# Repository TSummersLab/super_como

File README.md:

# Super COMO
Super COMO is an autonomous car platfrom at the University of Texas at Dallas. It is a hardware upgrade over the [COMO platform](https://github.com/TSummersLab/como).

Check out [our website](https://omarkabbas.github.io/supercomo/) for details about car assembly, build, and other guides and tutorials.

## Installation Guide

Before installing the Super COMO packages, perform a full JetPack installation on the Jetson TX2. For the package, JetPack 3.2.1 was installed. 

After installing JetPack, follow the steps below to setup Super COMO.

1. Configure repositories:
Configure repositories to allow "restricted," "universe," and "multiverse." Do this by following the instructions in [this link](https://help.ubuntu.com/community/Repositories/Ubuntu).

2. Clone super_como :
Clone the repository to your home directory. In a terminal window run:
```
cd ~ && git clone https://github.com/The-SS/super_como
```

3. Navigate to setup folder:
In terminal, navigate to the `setup` folder in `super_como` by running:
``` 
cd ~/super_como/setup
```

4. Configure git (if not configured):
Configure git either manually or by running `git_config_setup.sh`. You can run the setup file as follows:
```
./git_config_setup.sh
```

5. Run the following scripts:
```
./install_programs.sh

./install_ros.sh

```

6. Download and install the ZED SDK:
- Go to the [ZED downloads](https://www.stereolabs.com/developers/release/#sdkdownloads_anchor) website and download the [ZED SDK for Jetson TX2 with JetPack 3.2 and CUDA 9](https://download.stereolabs.com/zedsdk/2.7/tegrax2).

- Once it downloads, either used `chmod +x <file_name>` to make the file and executable or right click it --> permissions --> allow executing file as a program.

- Run the script by `cd` to file location in a terminal and typing `./` followed by the file name.

7. Setup the device rules:
Run the rules set up script:
```
sudo ./rules_setup.sh
```

This script will reload the rules, but we recommend restarting the machine to ensure that the rules are in effect.

8. Run the build script:
The `build.sh` script at the root of the super_como package builds the catkin workspace. In a terminal window, navigate to the root of the super_como package then run the following command:
```
cd ~/super_como
./build.sh
```

9. Generate the `ros_lib` libraries for arduino:
- Go the the Arduino `libraries` direcotry: 
```
cd ~/arduino-1.8.7/libraries
``` 
- Remove any previous `ros_lib` directory:
```
rm -fr ros_lib
```
- Generate the new libraries:
```
rosrun rosserial_arduino make_libraries.py .
```

For more details see the Install ros_lib into the Arduino Environment section [here](http://wiki.ros.org/rosserial_arduino/Tutorials/Arduino%20IDE%20Setup).

10. Source the workspace:
Every time a new terminal window is open you have to source your workspace.
```
source ~/super_como/workspace/devel/setup.bash
```
Alternatively, you can add the above to your bashrc file to avoid having to run it every time. To do that, run the following in a terminal.
```
echo "source ~/super_como/workspace/devel/setup.bash" >> ~/.bashrc
```
Once this runs you have to restart your terminal or source the bashrc file as follows:
```
source ~/.bashrc
```

11. Add the Lidar to ethernet networks:
- Open `Network Connections`.
- Click on `Add`.
- In the new window do the following:
	- Change the connection name to `lidar`
	- In the `General` tab, check the `Automatically connect to this network when it is available` and `All users may connect to this network` options
	- In the `IPv4 Settings` tab, change the `method` to `Manual` and add the following in `Addresses`:
		- address: 192.168.0.15
		- netmask: 255.255.255.0 (this will change to 24)
		- leave the `gateway` field empty
	- Click save.

12. Edit the USB port names:
The rules file generated by `rules_setup.sh` creates symbolic links for devices that should be used instead of the port names generated by Linux. The full list of symbolic links found in `/etc/udev/rules/99-device-rules.rules` is:
- `/dev/imu`: IMU
- `/dev/vesc`: VESC 
- `/dev/teensy`: Teensy
- `/dev/gps`: GPS module
- `/dev/elp/back`: back elp camera
- `/dev/elp/right`: righ elp camera
- `/dev/elp/left`: left elp camera
- `/dev/elp/front`: front elp camera

These links should be used in the package (instead of `/dev/ttyUSB*`, `/dev/ttyACM*`, or `/dev/video*`). Make the following modifications to the package:
- In `~/super_como/super_como/workspace/src/racecar/racecar/config/racecar-v2/vesc.yaml` change the `port` parameter under `vesc_driver` to `/dev/vesc`.
- In `~/super_como/workspace/src/razor_imu_9dof/config/razor.yaml` change the `port` parameter to `/dev/imu`.
- In `~/super_como/workspace/src/razor_imu_9dof/nodes/imu_node.py` change the `default_port` variable to `'/dev/imu'` (line 110). The updated line should be: `default_port='/dev/imu'`.

13. If running YOLO, change the `darknet_ros` camera topic: 
In `~/super_como/workspace/src/darknet_ros/darknet_ros/config/ros.yaml` change the `topic` parameter under `camera_reading` in `subscribers` to the desired image topic. For example that could be the `/zed/left/image_raw_color` topic if using the ZED or ZED mini cameras. Check the [YOLO github repository](https://github.com/leggedrobotics/darknet_ros/tree/7bc7ec0517b7107712da998f975584c88ed15f77) for more details.

## Operating the Package
Operating the package is a two step process:
1. Starting the sensors and hardware
2. Starting an autonomous feature
This decoupling allows for easy switching between autonomous features wihtout having to restart all sensor operation

#### To Start the Sensors and Hardware
1. Open `super_como/workspace/src/hardware_interface/launch/super_como.launch` and edit the `On/Off Switches` section (and save the changes). 
	- Setting the default value to `true` will start the component
	- Setting the default value to `false` will skip starting the component
2. Run the following in a terminal window:
```
roslaunch hardware_interface super_como.launch
```

The super_como.launch provides an all-in-one solution to starting all hardware components. Nonetheless, individual scripts can be launched. Any of the scripts in `super_como/workspace/src/hardware_interface/launch` or any of the other packages in workspace can be run individually to control a single (or multiple) device(s).

#### To Start an Autonomous Feature
1. Determine what application to run and edit the `super_como.launch` script to enable all the required sensors.
2. Run the appropriate launch file from `super_como/workspace/src/control/launch` to perform the desired feature by running the following in a terminal window: 
```
roslaunch control <file_name> 
```
Here, <file_name> is the desired launch file name.

Some of the autonomous features include the following:
- `hallway_navigation.launch`: requires the Hokuyo UST-10LX lidar
- `hallway_nav_wth_object_detection.launch`: requires the Hokuyo UST-10LX lidar and the camera used by `darknet_ros` (yolo) (ZED camear by default)
- `line_follower.launch`: requires the ZED camera
- `line_follower_with_lidar.launch`: requires the Hokuyo UST-10LX lidar and the ZED camera
- `darknet_ros.launch`: requires the camera used by `darknet_ros` (yolo) (ZED camear by default)

Other autonomous driving features can be designed similar to the first four included feature

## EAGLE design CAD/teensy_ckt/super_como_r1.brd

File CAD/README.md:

# CAD Files
CAD files for the Super COMO car.

# Description
- decks: 
	- Contains SolidWorks files (SLDPRT) for the decks and engineering drawings (PDF)
	- Machine the parts as follows:
		- Deck 1, Deck 2: Plastic
		- Deck 3: Aluminum
- elp_pole_mount:
	- Contains the stl files for the elp camera pole mount design (base and holder)
	- The original designer of these parts is Cheng Hao Yuan (chengyuan@berkeley.edu) and the parts are part of the [UCB BARC project](http://www.barc-project.com/) and can also be found [here](https://github.com/MPC-Berkeley/barc/tree/master/CAD/camera%20fixture)
	- 3D print the desired number using any material (ABS is fine)
- elp_seat_mount:
	- Contains the stl file for the elp camera seat mount design
	- The original designer of this part is Kevin Daniel (kmd140630@utdallas.edu)
	- 3D print the desired number using any material (ABS is fine)
- encoder_mount:
	- Contains the stl file and SolidWorks file (SLDPRT) for the encoder mount
 	- 3D print using any material (ABS is fine)
- encoder_disk:
	- Contains the stl file and SolidWorks file (SLDPRT) for the encoder disk
 	- 3D print using any material (ABS is fine)
- ultrasonic_mount:
	- Contains the stl file for the ultrasonic sensor mount (files/Ultraschallsensorhalterung_4.stl)
	- The original design is part of the Thingiverse database
	- 3D print using any material (ABS is fine)
- teensy_ckt:
	- Contains the Eagle board (BRD) and schematic (SCH) file, Gerber files, and PDFs
 for the teensy ckt
	- The schematic can be used to assemble the circuit. The Gerber files can be used to order the PCB.

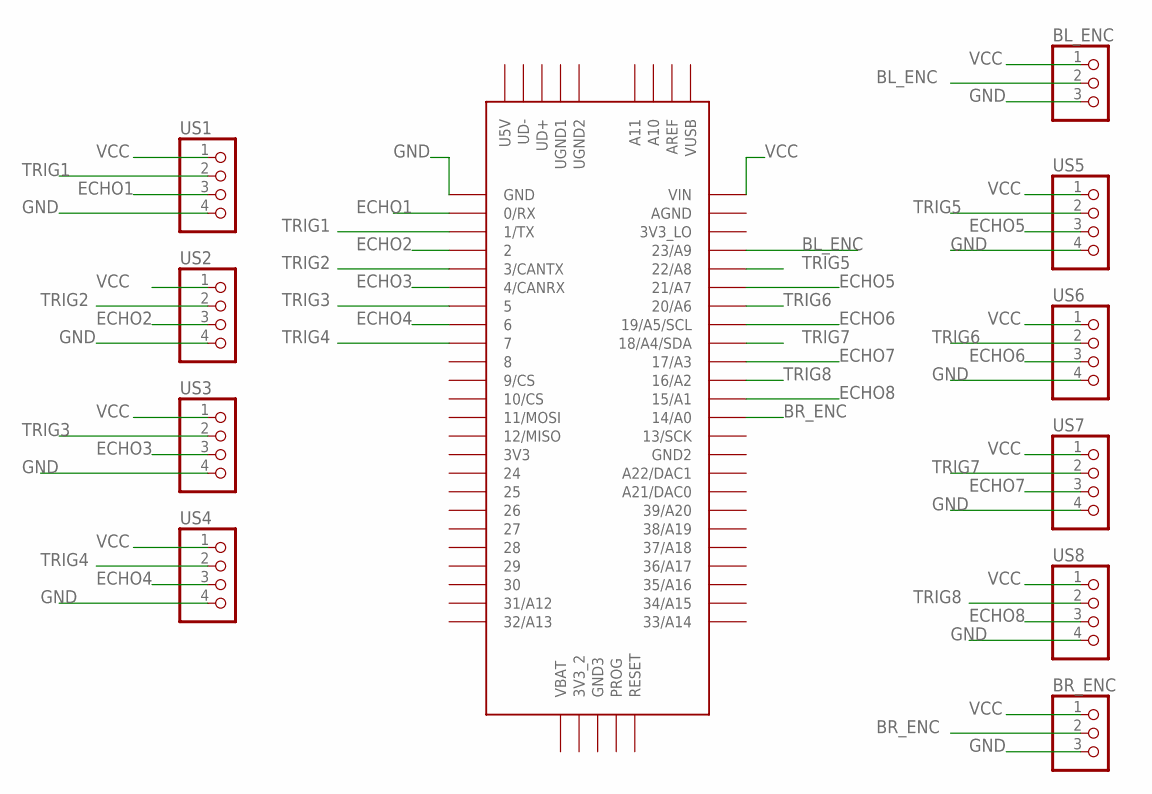
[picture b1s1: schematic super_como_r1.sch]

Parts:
BL_ENC: PINHD-1X3/90; 1X03/90
BR_ENC: PINHD-1X3/90; 1X03/90
U$1: TEENSY_3.5/3.6
US1, US2, US3, US4, US5, US6, US7, US8: PINHD-1X4/90; 1X04/90

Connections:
BL_ENC: BL_ENC.2, U$1.23/A9
BR_ENC: BR_ENC.2, U$1.14/A0
ECHO1: U$1.0/RX, US1.3
ECHO2: U$1.2, US2.3
ECHO3: U$1.4/CANRX, US3.3
ECHO4: U$1.6, US4.3
ECHO5: U$1.21/A7, US5.3
ECHO6: U$1.19/A5/SCL, US6.3
ECHO7: U$1.17/A3, US7.3
ECHO8: U$1.15/A1, US8.3
GND: BL_ENC.3, BR_ENC.3, U$1.GND, US1.4, US2.4, US3.4, US4.4, US5.4, US6.4, US7.4, US8.4
TRIG1: U$1.1/TX, US1.2
TRIG2: U$1.3/CANTX, US2.2
TRIG3: U$1.5, US3.2
TRIG4: U$1.7, US4.2
TRIG5: U$1.22/A8, US5.2
TRIG6: U$1.20/A6, US6.2
TRIG7: U$1.18/A4/SDA, US7.2
TRIG8: U$1.16/A2, US8.2
VCC: BL_ENC.1, BR_ENC.1, U$1.VIN, US1.1, US2.1, US3.1, US4.1, US5.1, US6.1, US7.1, US8.1

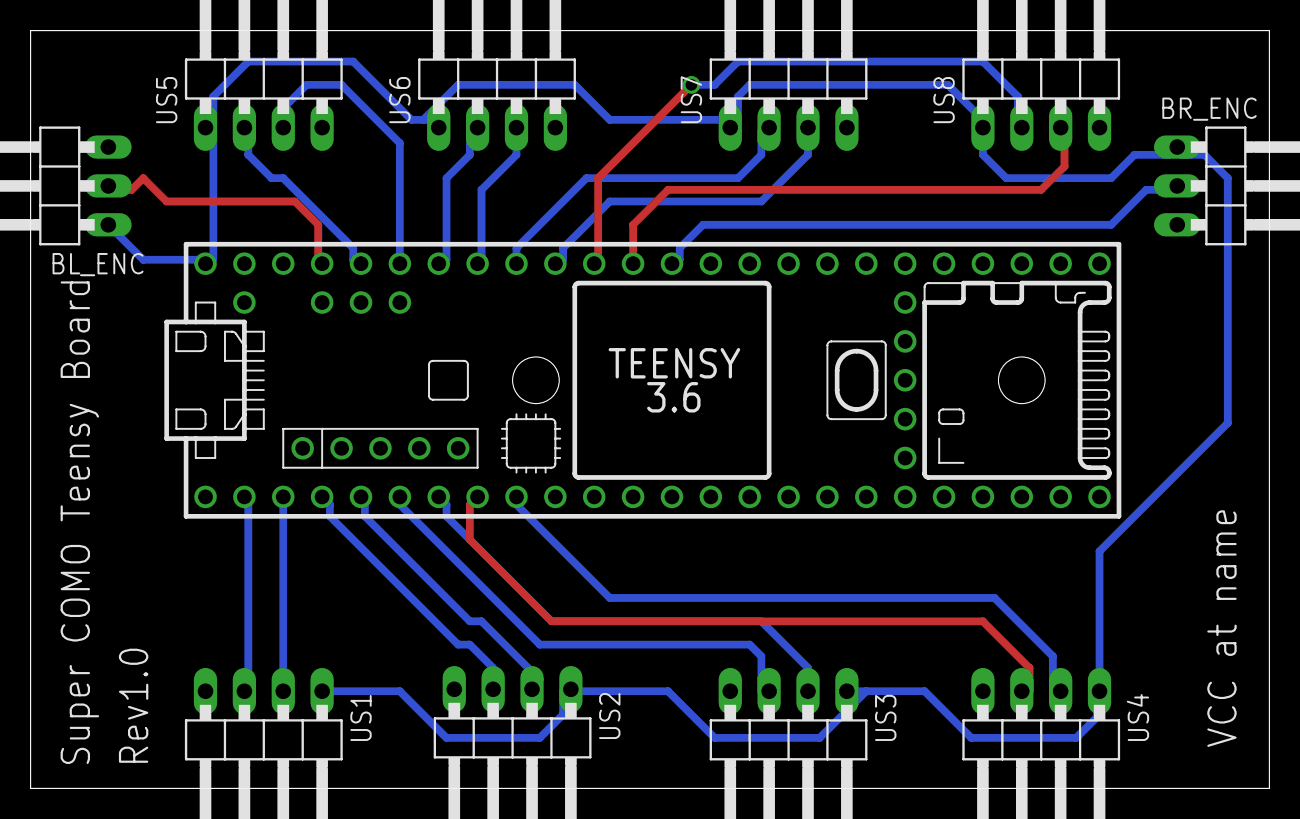
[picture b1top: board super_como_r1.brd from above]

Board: 2 copper layers, 81.0 x 49.5 mm, 11 parts (0 on the bottom side), 20 nets.

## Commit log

2018-06-18 initial commit; beginning of development
2018-06-26 adding git_config script and script to install software -part 1
2018-06-26 Adding ROS packages for joy and rviz to installer script
2018-06-28 minor changes to software_installer.sh
2018-07-12 adding catkin_tools
2018-07-16 Updating readme file and installer to add ZED installation
2018-10-31 Adding a workspace, a build script, and ZED ROS submodule
2018-10-31 minor edit
2018-11-01 Updating README file and software_installer
    Updating setup steps and adding Terminator installation to the software installer
2018-11-08 adding lidar and imu packages + modifications
2018-11-08 returning submodules
2019-02-06 Modifying setup files
2019-02-06 Adding MIT racecar packages as low-level control submodules
2019-02-06 Adding script to set up (USB) device rules
2019-02-07 Fixing bug in rules file
2019-03-25 backup before updating zed ros wrapper
2019-03-25 zed sdk updated to 2.7 and ros wrapper updated to newest version
2019-04-11 updates read file for recorder
2019-04-17 back up
2019-04-18 modifying some launch files
2019-04-18 Updating setup scripts
2019-04-19 removing rosserial clone
2019-04-19 removing darknet_rs and object_detection
2019-04-19 adding darknet_ros and updating setup scripts
2019-04-19 updating rules script and README file
2019-04-19 updating setup scripts
    adding image view
2019-04-19 updating hardware_interface launch files
2019-04-20 Adding CAD files
    adding some teensy arduino code too and editing readme files
2019-04-24 adding gps package
2019-04-25 updating teensy code + launch files
2019-04-29 Updating README file
2019-05-01 adding bill of materials
2019-05-02 updating launch files
2019-05-02 updating the README file
2019-05-07 folder_rename
2019-05-07 Create License
    Adding package license
